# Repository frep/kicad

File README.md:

kicad
=====
workspace for [kicad](http://www.kicad-pcb.org/) projects

Links
-----
* A starting point to work with kicad could be the the linked [tutorial](http://store.curiousinventor.com/guides/kicad).
* To convert pictures to silkscreen graphics (in kicad_mod format), I used the following [tool](http://img2mod.wayneandlayne.com/)
* To prepare the generated kicad files for the [Seeedstudio Fusion Service](http://www.seeedstudio.com/service/index.php?r=pcb), follow these [instructions](http://koblents.com/Ches/Original-Work/46-KiCAD---Seeedstudio-Fusion--Getting-Started/).  

Generation of gerber files
--------------------------
*Hi,*
*I had some trouble making a correct submission to the Seeedstudio Fusion service. Just for the sake of documentation* *in case somebody looks for information regarding this topic:*
*From my experience here are the parameters that work well with seeedstudio fusion service:*
*When exporting your PCB layout, select both coper layers, both solder mask layers, both silkscreen layers, and the* *edge cut layer.*
*Select "exclude edges from other layers" (sorry my version of kicad is in french and right now I can't make it work* *in english so the option's name is not necessarily exact).*
*In format, select "4.6"*
*In the Gerber options select the Protel extensions. It will generate the files with the correct extensions* *".GTL",".GTS", ...*

*To create the drill file I used "Units : inches", "Suppress leading* 
*zeros", postscript format (I don't know if that's useful), minimal*
*header", absolute coordinates.*

*Put all the generated files in a Zip archive, it should work. In case*
*it doesn't seeedstudio sends a mail indicating the error and you can *
*re-submit your files.*

**There is no need to rename the files.**

*I worked for me using 2 sided PCBs.*
*Hope it helps*

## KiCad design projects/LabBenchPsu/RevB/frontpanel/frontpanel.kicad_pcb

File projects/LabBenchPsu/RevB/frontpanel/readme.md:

Frontpanel
==========

Working:
--------
 * reading buttons and encoders over gpio-expander
 * TPS2513: Loading iPhone (1A), iPad (1.5A)

Not working:
------------
 * LiPo charging indicators (2 leds) worked first, but not anymore. Maybe too low current resistor used?
 * Load on  indicator on the gpio-expander not working. Probably signal too low since it's taken after loadOn-diode.

More or less working:
---------------------
 * LiPo charger with different load currents works up to about 500mA. Imo it should work up to 1000mA. 

Not yet tested:
---------------
 * TPS2513: Loading android devices

Improvements for a next revision:
---------------------------------
 * Placement of the gpio-expander: out of the way from the display
 * LoadOn - signal should be read out correct.
 * Maybe adding an ina219 for measuring the load current of the LiPo charger. With this feedback, loadcurrent could be controlled.
 * Screw terminal have quite small diameters. Maybe use bigger ones or more of them (at least for 5V)

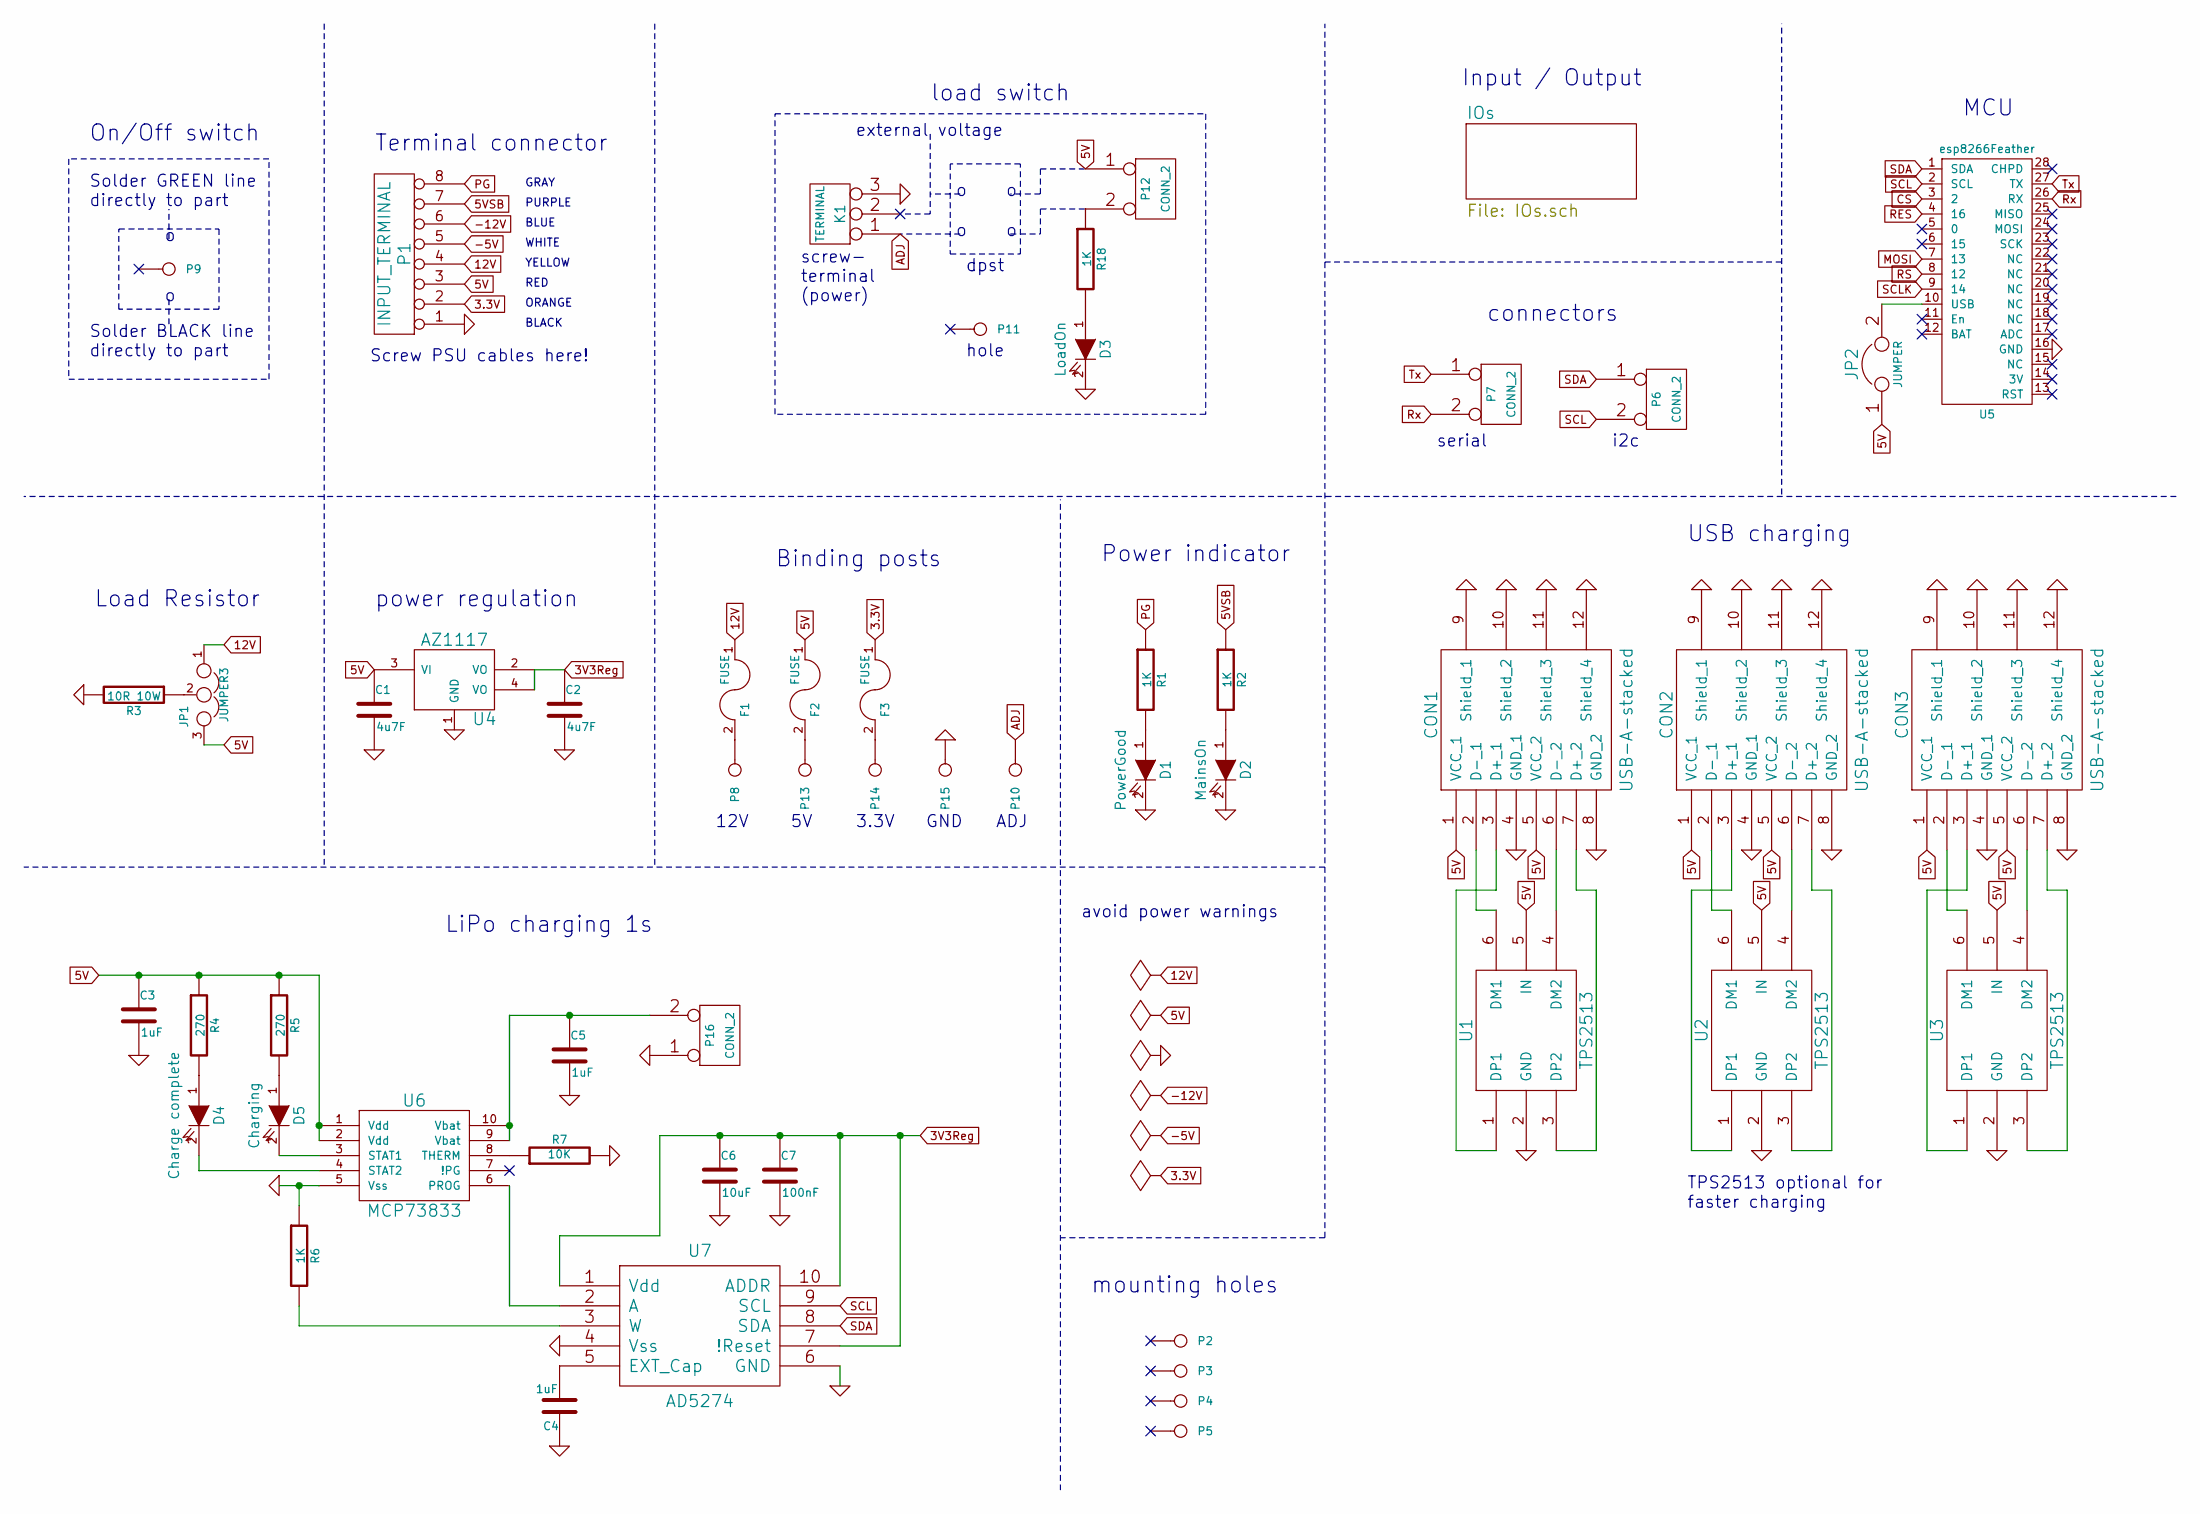
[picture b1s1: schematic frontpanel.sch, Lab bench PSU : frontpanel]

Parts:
C1, C2: 4u7F; C0805
C3, C4, C5: 1uF; C0805
C6: 10uF; C0805
C7: 100nF; C0805
CON1, CON2, CON3: USB-A-stacked; USB-A-Stacked
D1: PowerGood; LED-0805
D2: MainsOn; LED-0805
D3: LoadOn; LED-0805
D4: Charge complete; LED-0805
D5: Charging; LED-0805
F1, F2, F3: FUSE; C1812
JP1: JUMPER3; Pin_Proto_Straight_1x03
JP2: JUMPER; Pin_Proto_Straight_1x02
K1: TERMINAL; terminal_3p5mm_3pin
P1: INPUT_TERMINAL; terminal_3p5mm_8pin
P2, P3, P4, P5: MH; MountingHole_3mm
P6, P7, P12: CONN_2; Pin_Proto_Straight_1x02
P8, P10, P13, P14, P15: BindingPost
P9: OnOffSwitch; RockerSwitch
P11: LoadSwitch
P16: CONN_2; JST-PH-2-THM
R1, R2, R6, R18: 1K; R0805
R3: 10R 10W; R_ceramic_48x9p5x9mm
R4, R5: 270; R0805
R7: 10K; R0805
U1, U2, U3: TPS2513; SOT23-6
U4: AZ1117; SOT223
U5: esp8266Feather; featherEsp
U6: MCP73833; MSOP10
U7: AD5274; MSOP10

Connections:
3.3V: F3.1, P1.2
3V3Reg: C2.1, C6.1, C7.1, U4.2 (VO), U4.4 (VO), U7.1 (Vdd), U7.7 (!Reset), U7.10 (ADDR); also elsewhere on the board
5V: C1.1, C3.1, CON1.1 (VCC_1), CON1.5 (VCC_2), CON2.1 (VCC_1), CON2.5 (VCC_2), CON3.1 (VCC_1), CON3.5 (VCC_2), F2.1, JP1.3, JP2.1, P1.3, P12.1, R4.1, R5.1, U1.5 (IN), U2.5 (IN), U3.5 (IN), U4.3 (VI), U6.1 (Vdd), U6.2 (Vdd)
5VSB: P1.7, R2.1
12V: F1.1, JP1.1, P1.4
-5V: P1.5
-12V: P1.6
ADJ: K1.1, P10.1
CS: U5.3 (2); also elsewhere on the board
GND: C1.2, C2.2, C3.2, C4.1, C5.2, C6.2, C7.2, CON1.4 (GND_1), CON1.8 (GND_2), CON1.9 (Shield_1), CON1.10 (Shield_2), CON1.11 (Shield_3), CON1.12 (Shield_4), CON2.4 (GND_1), CON2.8 (GND_2), CON2.9 (Shield_1), CON2.10 (Shield_2), CON2.11 (Shield_3), CON2.12 (Shield_4), CON3.4 (GND_1), CON3.8 (GND_2), CON3.9 (Shield_1), CON3.10 (Shield_2), CON3.11 (Shield_3), CON3.12 (Shield_4), D1.2 (K), D2.2 (K), D3.2 (K), K1.3, P1.1, P15.1, P16.1, R3.2, R6.1, R7.2, U1.2 (GND), U2.2 (GND), U3.2 (GND), U4.1 (GND), U5.16 (GND), U6.5 (Vss), U7.4 (Vss), U7.6 (GND); also elsewhere on the board
MOSI: U5.7 (13); also elsewhere on the board
unnamed: C4.2, U7.5 (EXT_Cap)
unnamed: C5.1, P16.2 (PM), U6.9 (Vbat), U6.10 (Vbat)
unnamed: CON1.2 (D-_1), U1.6 (DM1)
unnamed: CON1.3 (D+_1), U1.1 (DP1)
unnamed: CON1.6 (D-_2), U1.4 (DM2)
unnamed: CON1.7 (D+_2), U1.3 (DP2)
unnamed: CON2.2 (D-_1), U2.6 (DM1)
unnamed: CON2.3 (D+_1), U2.1 (DP1)
unnamed: CON2.6 (D-_2), U2.4 (DM2)
unnamed: CON2.7 (D+_2), U2.3 (DP2)
unnamed: CON3.2 (D-_1), U3.6 (DM1)
unnamed: CON3.3 (D+_1), U3.1 (DP1)
unnamed: CON3.6 (D-_2), U3.4 (DM2)
unnamed: CON3.7 (D+_2), U3.3 (DP2)
unnamed: D1.1 (A), R1.2
unnamed: D2.1 (A), R2.2
unnamed: D3.1 (A), R18.2
unnamed: D4.1 (A), R4.2
unnamed: D4.2 (K), U6.4 (STAT2)
unnamed: D5.1 (A), R5.2
unnamed: D5.2 (K), U6.3 (STAT1)
unnamed: F1.2, P8.1
unnamed: F2.2, P13.1
unnamed: F3.2, P14.1
unnamed: JP1.2, R3.1
unnamed: JP2.2, U5.10 (USB)
unnamed: P12.2 (PM), R18.1
unnamed: R6.2, U7.3 (W)
unnamed: R7.1, U6.8 (THERM)
unnamed: U6.6 (PROG), U7.2 (A)
PG: P1.8, R1.1
RES: U5.4 (16); also elsewhere on the board
RS: U5.8 (12); also elsewhere on the board
Rx: P7.2 (PM), U5.26 (RX)
SCL: P6.2 (PM), U5.2 (SCL), U7.9 (SCL); also elsewhere on the board
SCLK: U5.9 (14); also elsewhere on the board
SDA: P6.1, U5.1 (SDA), U7.8 (SDA); also elsewhere on the board
Tx: P7.1, U5.27 (TX)

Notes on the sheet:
Solder GREEN line directly to part
Solder BLACK line directly to part
Terminal connector
GRAY
PURPLE
BLUE
WHITE
YELLOW
RED
ORANGE
BLACK
Load Resistor
mounting holes
serial
i2c
avoid power warnings
Binding posts
load switch
screw- terminal (power)
hole
12V
3.3V
GND
ADJ
dpst
external voltage
MCU
TPS2513 optional for faster charging
On/Off switch
LiPo charging 1s
USB charging
power regulation
connectors
Screw PSU cables here!
Input / Output
Power indicator

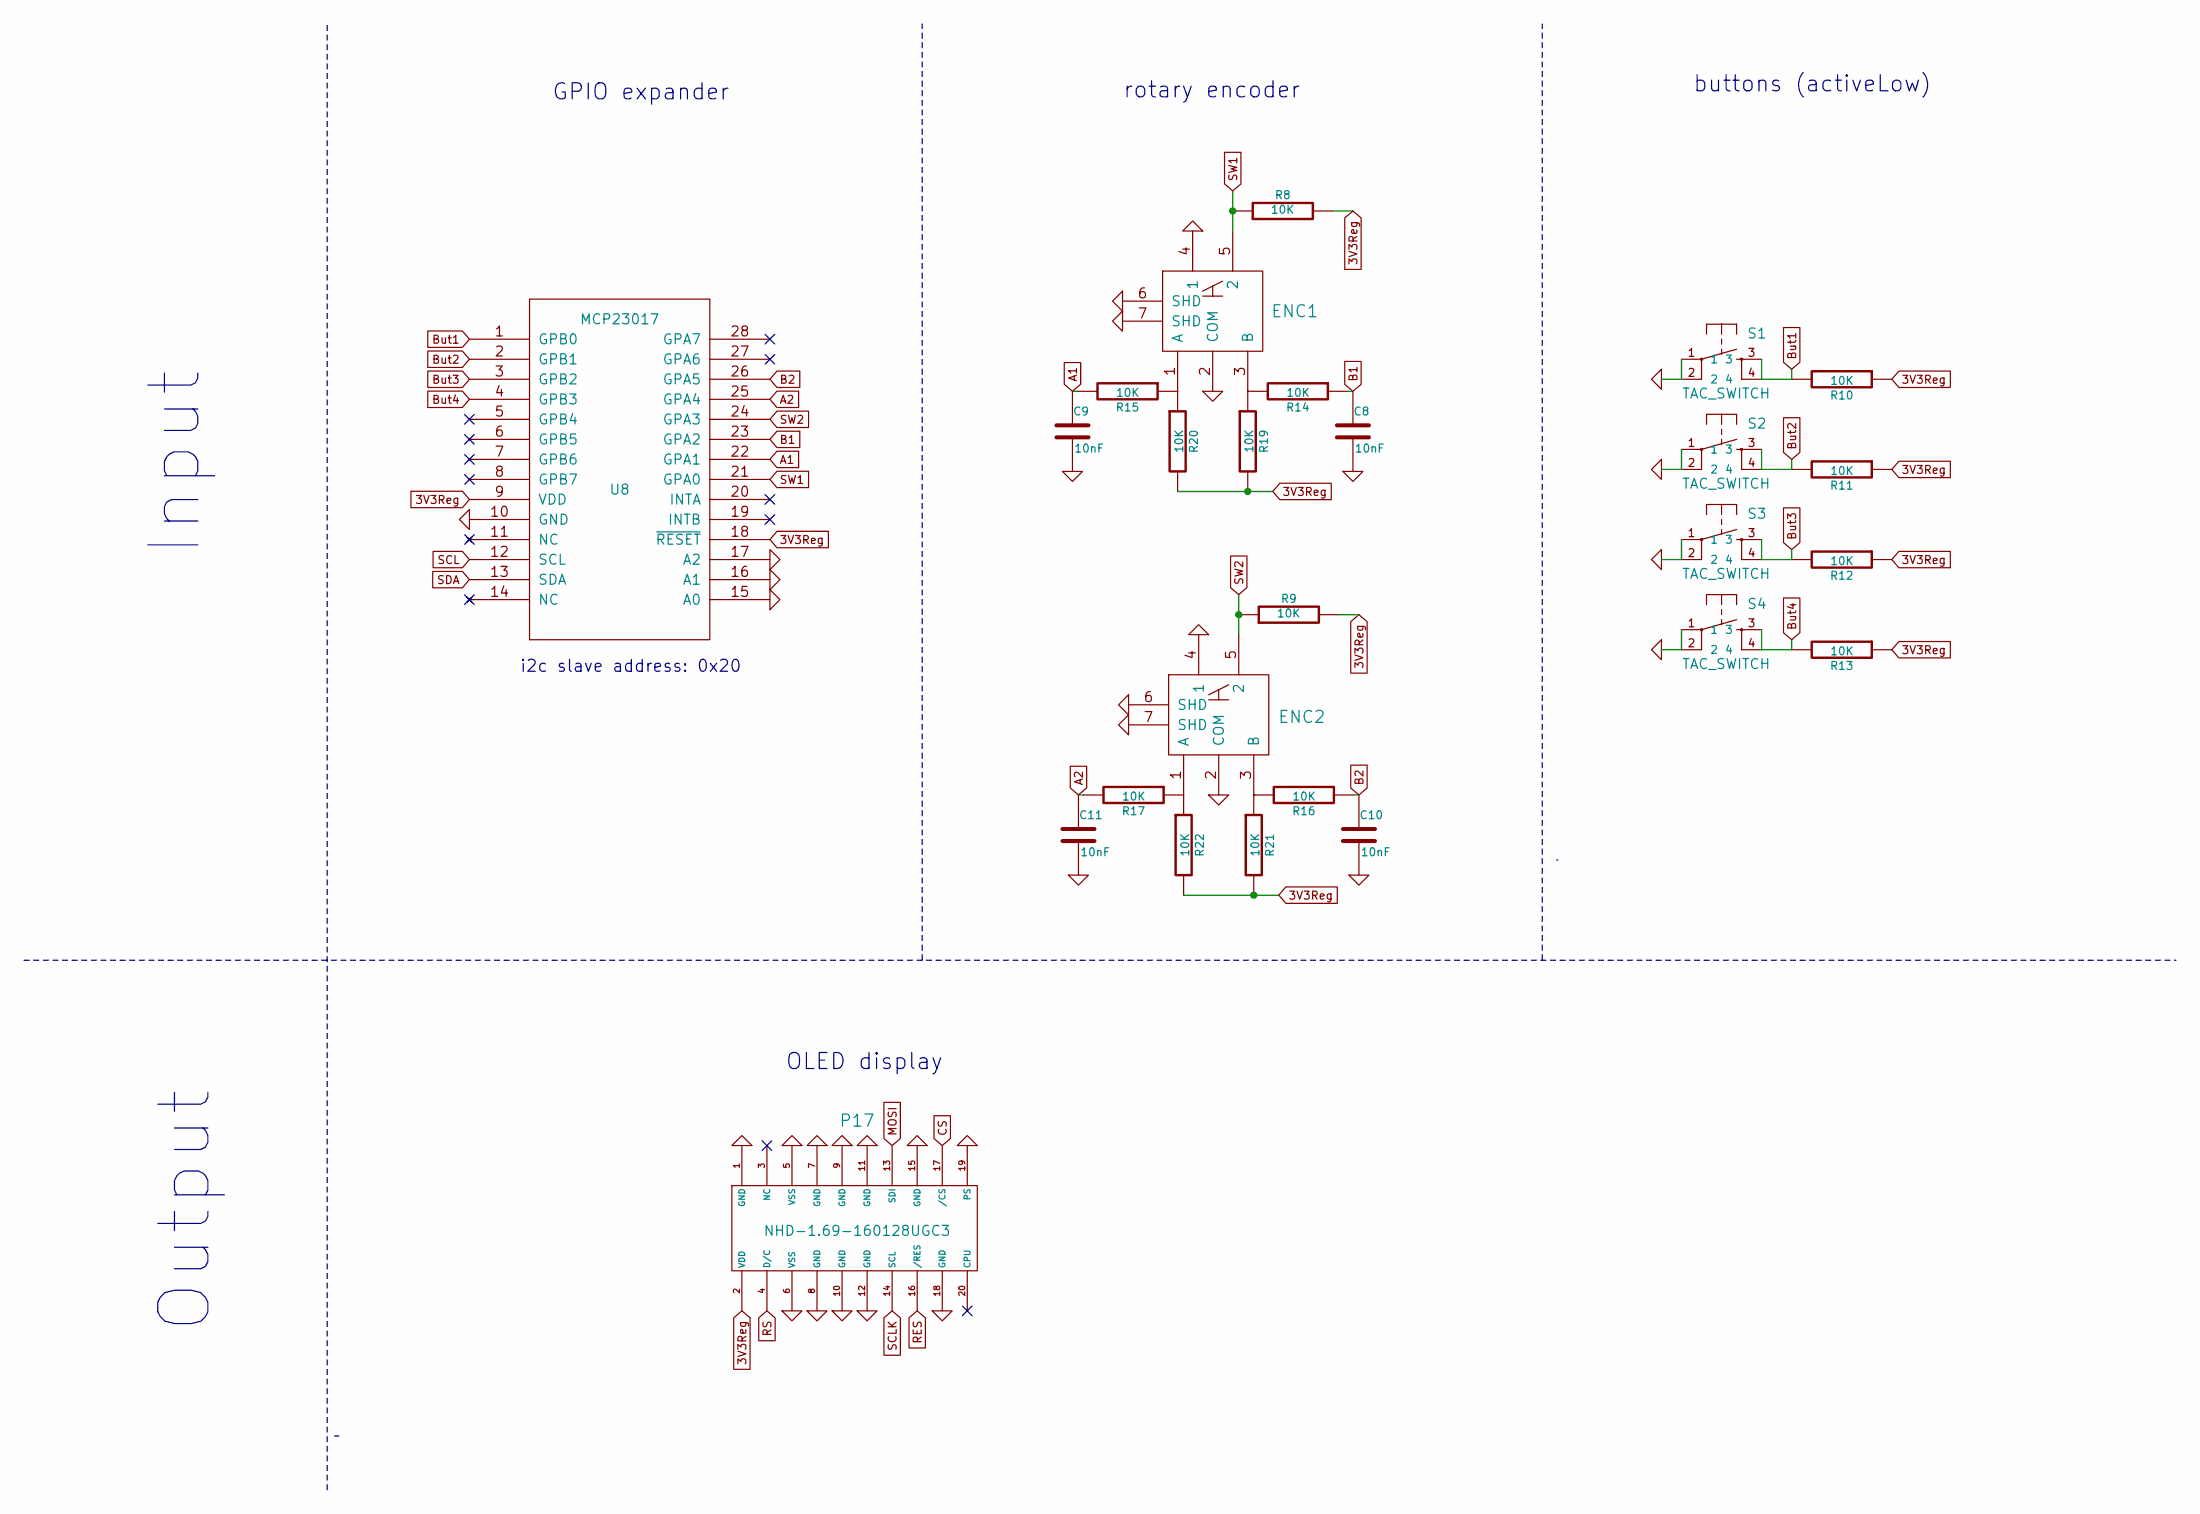
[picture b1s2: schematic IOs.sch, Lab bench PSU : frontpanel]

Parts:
C8, C9, C10, C11: 10nF; C0805
ENC1, ENC2: RotaryEncoder
P17: NHD-1.69-160128UGC3
R8, R9, R10, R11, R12, R13, R14, R15, R16, R17, R19, R20, R21, R22: 10K; R0805
S1, S2, S3, S4: TAC_SWITCH; TACTILE-PTH
U8: MCP23017; SOIC28W

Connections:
3V3Reg: P17.2 (VDD), R8.2, R9.2, R10.1, R11.1, R12.1, R13.1, R19.2, R20.2, R21.2, R22.2, U8.9 (VDD), U8.18 (~RESET); also elsewhere on the board
A1: C9.1, R15.2, U8.22 (GPA1)
A2: C11.1, R17.2, U8.25 (GPA4)
B1: C8.1, R14.1, U8.23 (GPA2)
B2: C10.1, R16.1, U8.26 (GPA5)
But1: R10.2, S1.3, S1.4, U8.1 (GPB0)
But2: R11.2, S2.3, S2.4, U8.2 (GPB1)
But3: R12.2, S3.3, S3.4, U8.3 (GPB2)
But4: R13.2, S4.3, S4.4, U8.4 (GPB3)
CS: P17.17 (/CS); also elsewhere on the board
GND: C8.2, C9.2, C10.2, C11.2, ENC1.2 (COM), ENC1.4 (1), ENC1.6 (SHD), ENC1.7 (SHD), ENC2.2 (COM), ENC2.4 (1), ENC2.6 (SHD), ENC2.7 (SHD), P17.1 (GND), P17.5 (VSS), P17.6 (VSS), P17.7 (GND), P17.8 (GND), P17.9 (GND), P17.10 (GND), P17.11 (GND), P17.12 (GND), P17.15 (GND), P17.18 (GND), P17.19 (PS), S1.1, S1.2, S2.1, S2.2, S3.1, S3.2, S4.1, S4.2, U8.10 (GND), U8.15 (A0), U8.16 (A1), U8.17 (A2); also elsewhere on the board
MOSI: P17.13 (SDI); also elsewhere on the board
unnamed: ENC1.1 (A), R15.1, R20.1
unnamed: ENC1.3 (B), R14.2, R19.1
unnamed: ENC2.1 (A), R17.1, R22.1
unnamed: ENC2.3 (B), R16.2, R21.1
RES: P17.16 (/RES); also elsewhere on the board
RS: P17.4 (D/C); also elsewhere on the board
SCL: U8.12 (SCL); also elsewhere on the board
SCLK: P17.14 (SCL); also elsewhere on the board
SDA: U8.13 (SDA); also elsewhere on the board
SW1: ENC1.5 (2), R8.1, U8.21 (GPA0)
SW2: ENC2.5 (2), R9.1, U8.24 (GPA3)

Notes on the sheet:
buttons (activeLow)
i2c slave address: 0x20
OLED display
Output
Input
GPIO expander
rotary encoder

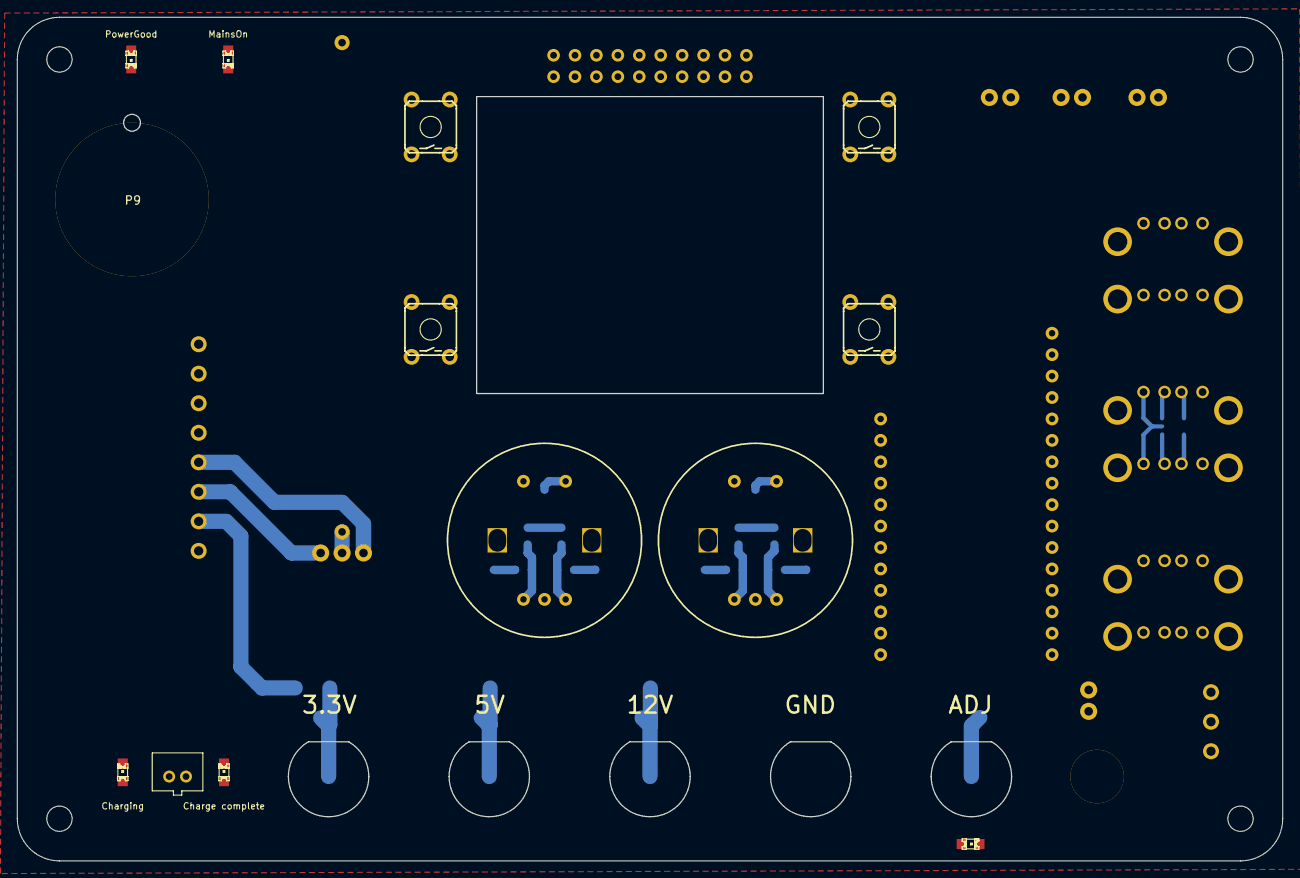
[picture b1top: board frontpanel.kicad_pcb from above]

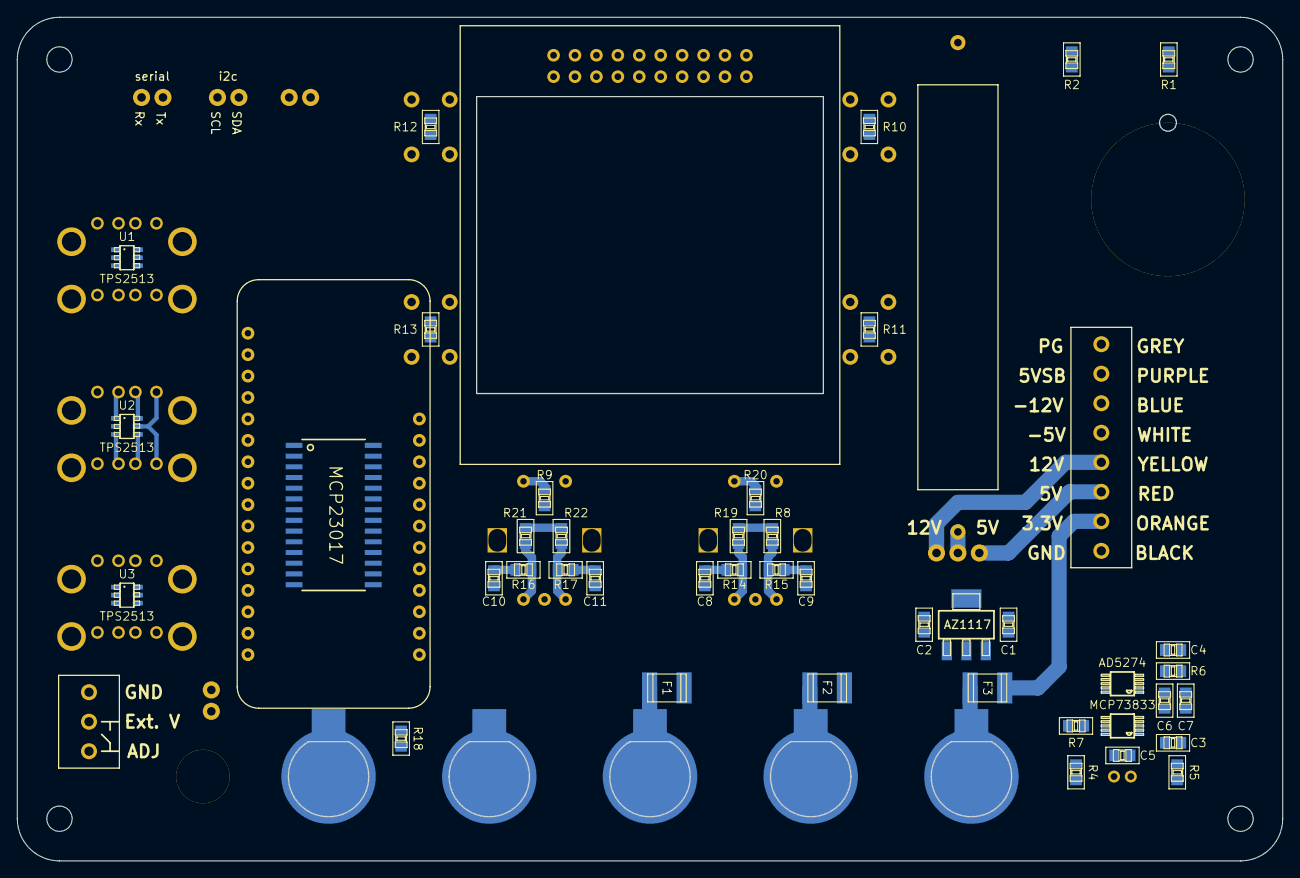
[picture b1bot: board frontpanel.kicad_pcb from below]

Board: 2 copper layers, 150.0 x 100.0 mm, 78 parts (54 on the bottom side), 61 nets.

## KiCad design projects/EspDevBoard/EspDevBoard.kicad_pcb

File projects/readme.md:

Projects
========
The following projects contains a pcb designed with kicad. All the needed schematics and footprints can be found in the library folder.   

Radxa Arduino Shield
--------------------
The RAS (Radxa Arduino Shield) is an addon-shield for the radxa rock (pro). It contains an arduino micro clone running at 3.3V connected over i2c with the radxa. The shield also includes an OLED 16x2 char display, also connected over i2c. It can be used by the radxa or the arduino.   

Lab bench PSU
-------------
A current-controlled, voltage-controlled lab bench psu based on the [usupply](http://www.eevblog.com/projects/usupply/) from David Jones. Instead of being portable, my focus is to transform an old pc-psu into an lab bench psu.

Arduino Controller
------------------
An Arduino-clone of the Arduino Esplora. I removed the things I didn't like and added some other features instead. 

PowerBox
--------
LiPo-cell in a box. Based on the Adafruit PowerBoost 1000 Charger. Charge Lipo-cell, power usb-devices from Lipo or use lipo as USP.
Measure Voltage and current drawn by the load. Autoshutdown, when critical lipo-voltage is reached.

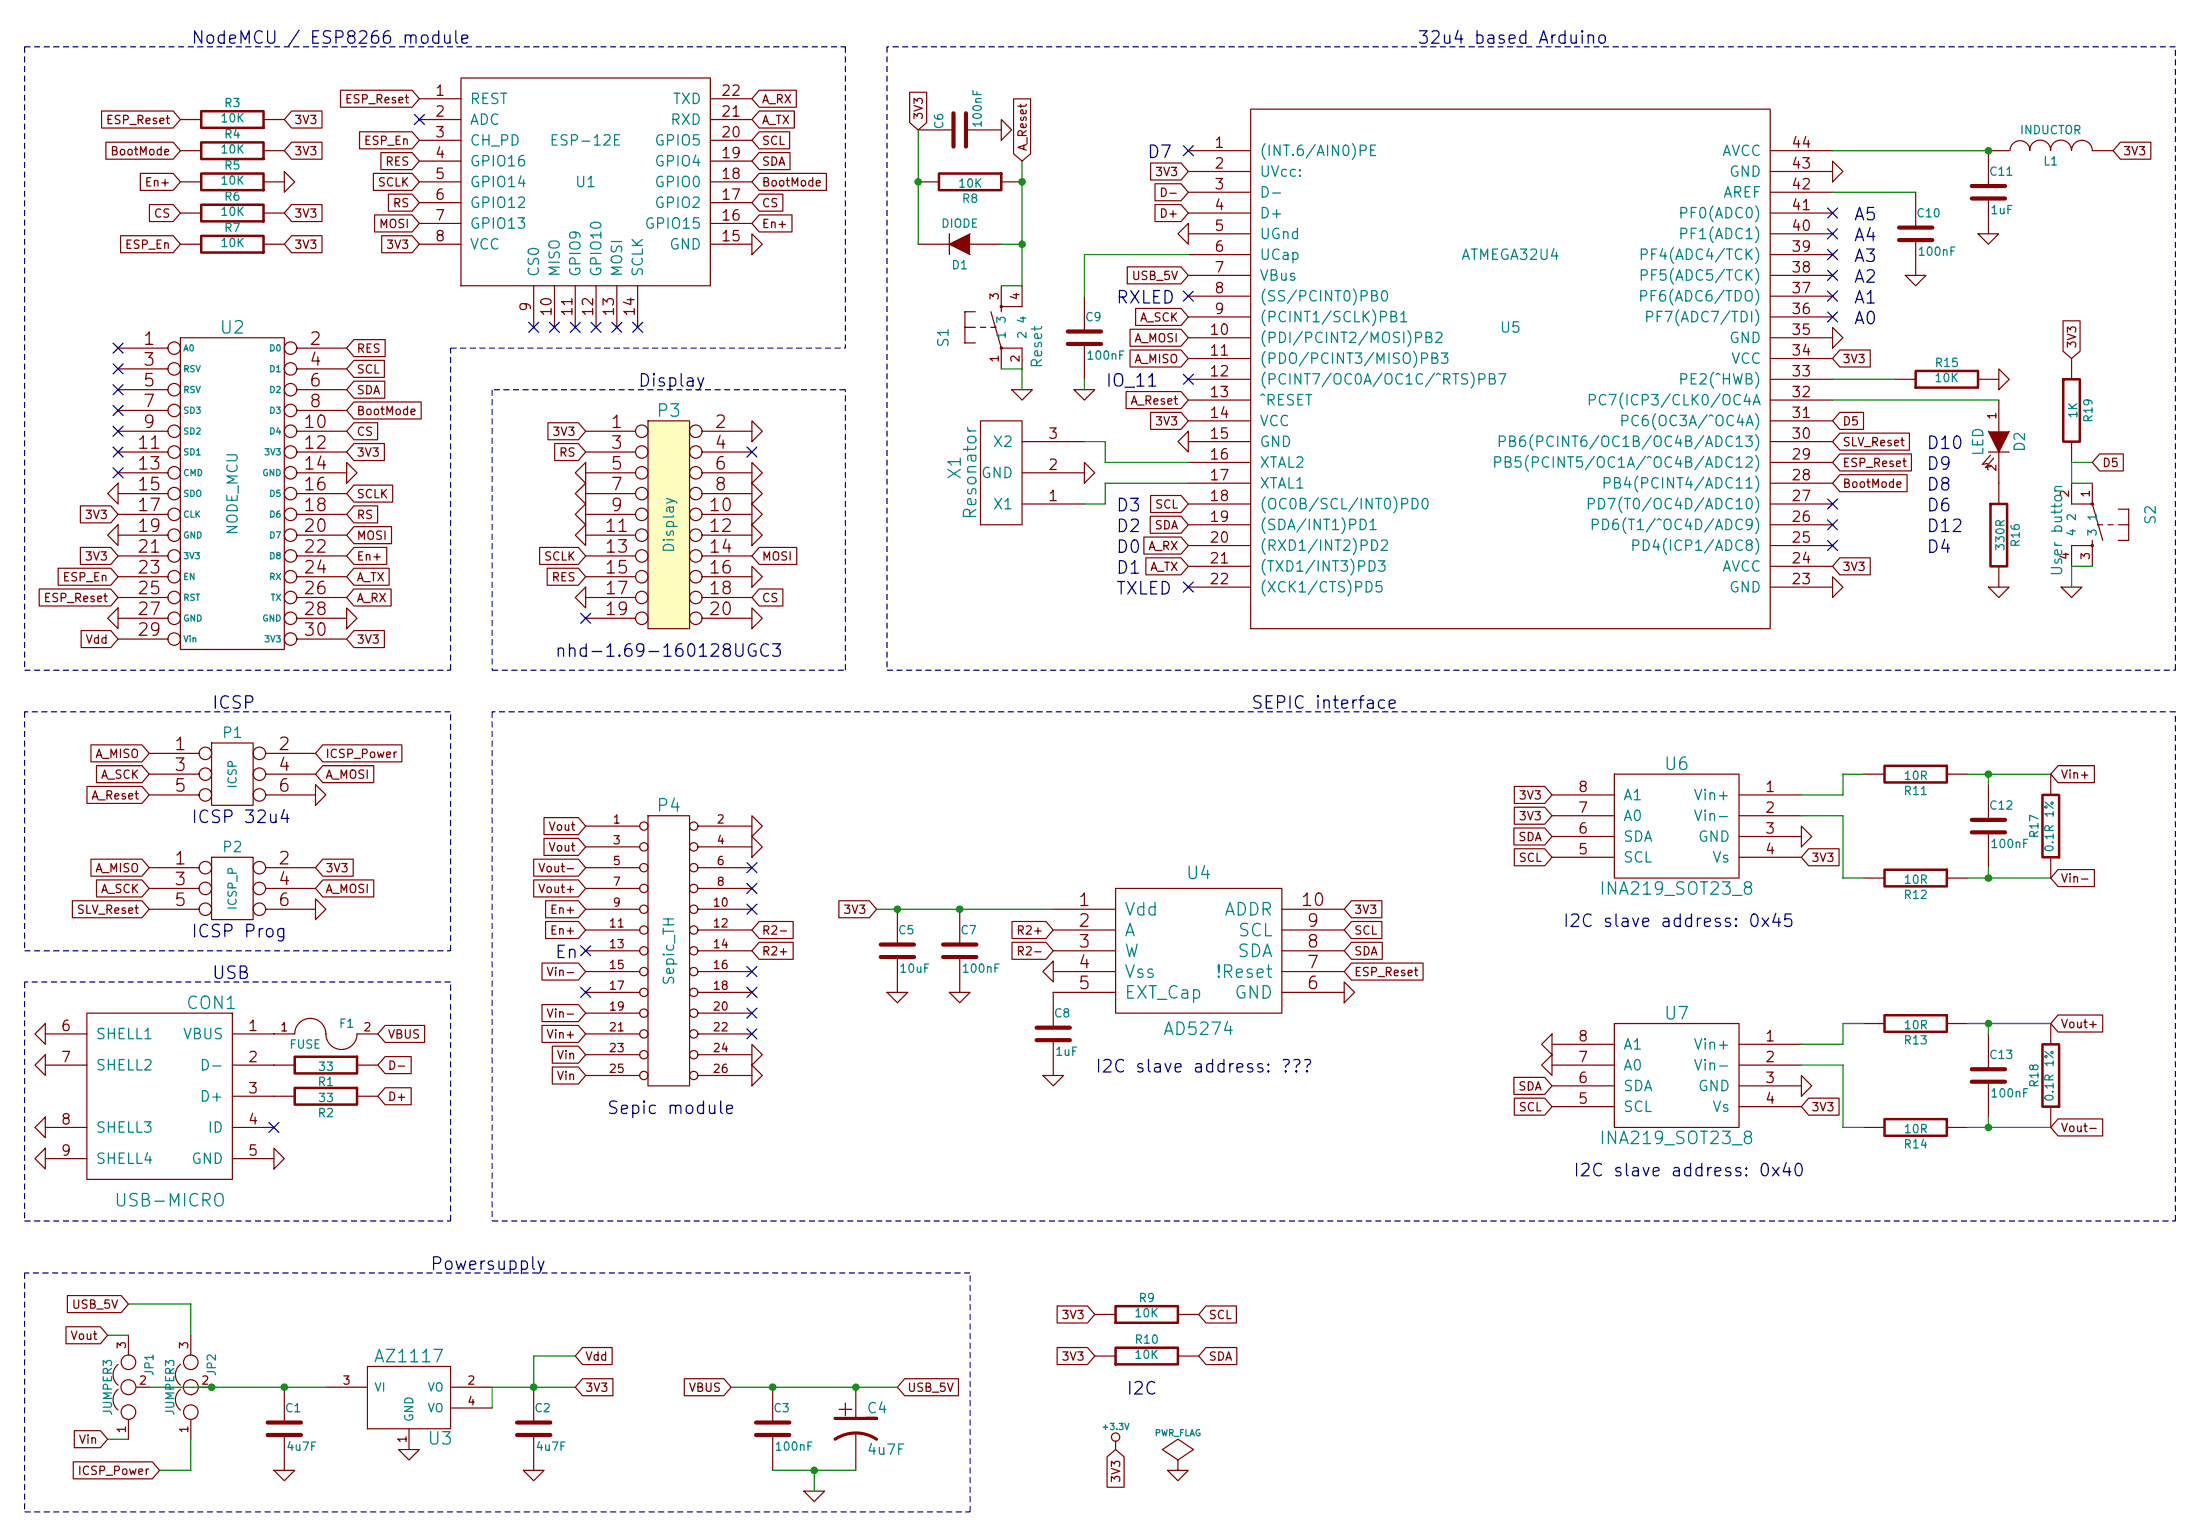
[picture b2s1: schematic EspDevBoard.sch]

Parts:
C1, C2, C4: 4u7F; C0805
C3, C6, C7, C9, C10, C12, C13: 100nF; C0805
C5: 10uF; C0805
C8, C11: 1uF; C0805
CON1: USB-MICRO; USB_Micro
D1: DIODE; Diode-MiniMELF_Handsoldering
D2: LED; LED-0805
F1: FUSE; C1812
JP1, JP2: JUMPER3; Pin_Proto_Straight_1x03
L1: INDUCTOR; C0805
P1: ICSP; Pin_Proto_Straight_2x03
P2: ICSP_P; Pin_Proto_Straight_2x03
P3: Display; Pin_Proto_Straight_2x10
P4: Sepic_TH
R1, R2: 33; R0805
R3, R4, R5, R6, R7, R8, R9, R10, R15: 10K; R0805
R11, R12, R13, R14: 10R; R0805
R16: 330R; R0805
R17, R18: 0.1R 1%; R1206
R19: 1K; R0805
S1: Reset; TACTILE-PTH
S2: User button; TACTILE-PTH
U1: ESP-12E
U2: NODE_MCU; NodeMcu
U3: AZ1117; SOT223
U4: AD5274; MSOP10
U5: ATMEGA32U4; TQFP44
U6, U7: INA219_SOT23_8; SOT-23-8
X1: Resonator

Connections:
3V3: C2.1, C5.1, C6.1, C7.1, D1.2 (K), L1.2, P2.2, P3.1, R3.1, R4.1, R6.1, R7.1, R8.2, R9.1, R10.1, R19.1, U1.8 (VCC), U2.12 (3V3), U2.17 (CLK), U2.21 (3V3), U2.29 (Vin), U2.30 (3V3), U3.2 (VO), U3.4 (VO), U4.1 (Vdd), U4.10 (ADDR), U5.2 (UVcc:), U5.14 (VCC), U5.24 (AVCC), U5.34 (VCC), U6.4 (Vs), U6.7 (A0), U6.8 (A1), U7.4 (Vs)
A_MISO: P1.1, P2.1, U5.11 ((PDO/PCINT3/MISO)PB3)
A_MOSI: P1.4, P2.4, U5.10 ((PDI/PCINT2/MOSI)PB2)
A_RX: U1.22 (TXD), U2.26 (TX), U5.20 ((RXD1/INT2)PD2)
A_Reset: D1.1 (A), P1.5, R8.1, S1.3, S1.4, U5.13 (^RESET)
A_SCK: P1.3, P2.3, U5.9 ((PCINT1/SCLK)PB1)
A_TX: U1.21 (RXD), U2.24 (RX), U5.21 ((TXD1/INT3)PD3)
BootMode: R4.2, U1.18 (GPIO0), U2.8 (D3), U5.28 (PB4(PCINT4/ADC11))
CS: P3.18, R6.2, U1.17 (GPIO2), U2.10 (D4)
D5: R19.2, S2.1, S2.2, U5.31 (PC6(OC3A/^OC4A))
D+: R2.1, U5.4 (D+)
D-: R1.1, U5.3 (D-)
ESP_En: R7.2, U1.3 (CH_PD), U2.23 (EN)
ESP_Reset: R3.2, U1.1 (REST), U2.25 (RST), U4.7 (!Reset), U5.29 (PB5(PCINT5/OC1A/^OC4B/ADC12))
En+: P4.9, P4.11, R5.2, U1.16 (GPIO15), U2.22 (D8)
GND: C1.2, C2.2, C3.2, C4.2, C5.2, C6.2, C7.2, C8.2, C9.2, C10.2, C11.2, CON1.5 (GND), CON1.6 (SHELL1), CON1.7 (SHELL2), CON1.8 (SHELL3), CON1.9 (SHELL4), P1.6, P2.6, P3.2, P3.5, P3.6, P3.7, P3.8, P3.9, P3.10, P3.11, P3.12, P3.16, P3.17, P3.20, P4.2, P4.4, P4.24 (P20), P4.26 (P22), R5.1, R15.2, R16.2, S1.1, S1.2, S2.3, S2.4, U1.15 (GND), U2.14 (GND), U2.15 (SDO), U2.19 (GND), U2.27 (GND), U2.28 (GND), U3.1 (GND), U4.4 (Vss), U4.6 (GND), U5.5 (UGnd), U5.15 (GND), U5.23 (GND), U5.35 (GND), U5.43 (GND), U6.3 (GND), U7.3 (GND), U7.7 (A0), U7.8 (A1), X1.2 (GND)
ICSP_Power: JP2.1, P1.2
MOSI: P3.14, U1.7 (GPIO13), U2.20 (D7)
unnamed: C1.1, JP1.2, JP2.2, U3.3 (VI)
unnamed: C8.1, U4.5 (EXT_Cap)
unnamed: C9.1, U5.6 (UCap)
unnamed: C10.1, U5.42 (AREF)
unnamed: C11.1, L1.1, U5.44 (AVCC)
unnamed: CON1.1 (VBUS), F1.1
unnamed: CON1.2 (D-), R1.2
unnamed: CON1.3 (D+), R2.2
unnamed: D2.1 (A), U5.32 (PC7(ICP3/CLK0/OC4A)
unnamed: D2.2 (K), R16.1
unnamed: R11.2, U6.1 (Vin+)
unnamed: R12.2, U6.2 (Vin-)
unnamed: R13.2, U7.1 (Vin+)
unnamed: R14.2, U7.2 (Vin-)
unnamed: R15.1, U5.33 (PE2(^HWB))
unnamed: U5.16 (XTAL2), X1.3 (X2)
unnamed: U5.17 (XTAL1), X1.1 (X1)
R2+: P4.14, U4.2 (A)
R2-: P4.12, U4.3 (W)
RES: P3.15, U1.4 (GPIO16), U2.2 (D0)
RS: P3.3, U1.6 (GPIO12), U2.18 (D6)
SCL: R9.2, U1.20 (GPIO5), U2.4 (D1), U4.9 (SCL), U5.18 ((OC0B/SCL/INT0)PD0), U6.5 (SCL), U7.5 (SCL)
SCLK: P3.13, U1.5 (GPIO14), U2.16 (D5)
SDA: R10.2, U1.19 (GPIO4), U2.6 (D2), U4.8 (SDA), U5.19 ((SDA/INT1)PD1), U6.6 (SDA), U7.6 (SDA)
SLV_Reset: P2.5, U5.30 (PB6(PCINT6/OC1B/OC4B/ADC13))
VBUS: C3.1, C4.1, F1.2, JP2.3, U5.7 (VBus)
Vin: JP1.1, P4.23, P4.25 (P24)
Vin+: C12.1, P4.21, R11.1, R17.2
Vin-: C12.2, P4.15, P4.19, R12.1, R17.1
Vout: JP1.3, P4.1, P4.3
Vout+: C13.1, P4.7, R13.1, R18.2
Vout-: C13.2, P4.5, R14.1, R18.1

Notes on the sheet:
Display
Sepic module
ICSP 32u4
I2C
I2C slave address: 0x40
I2C slave address: 0x45
ICSP Prog
I2C slave address: ???
RXLED
TXLED
D10
D12
ICSP
NodeMCU / ESP8266 module
USB
32u4 based Arduino
SEPIC interface
Powersupply
nhd-1.69-160128UGC3
IO_11

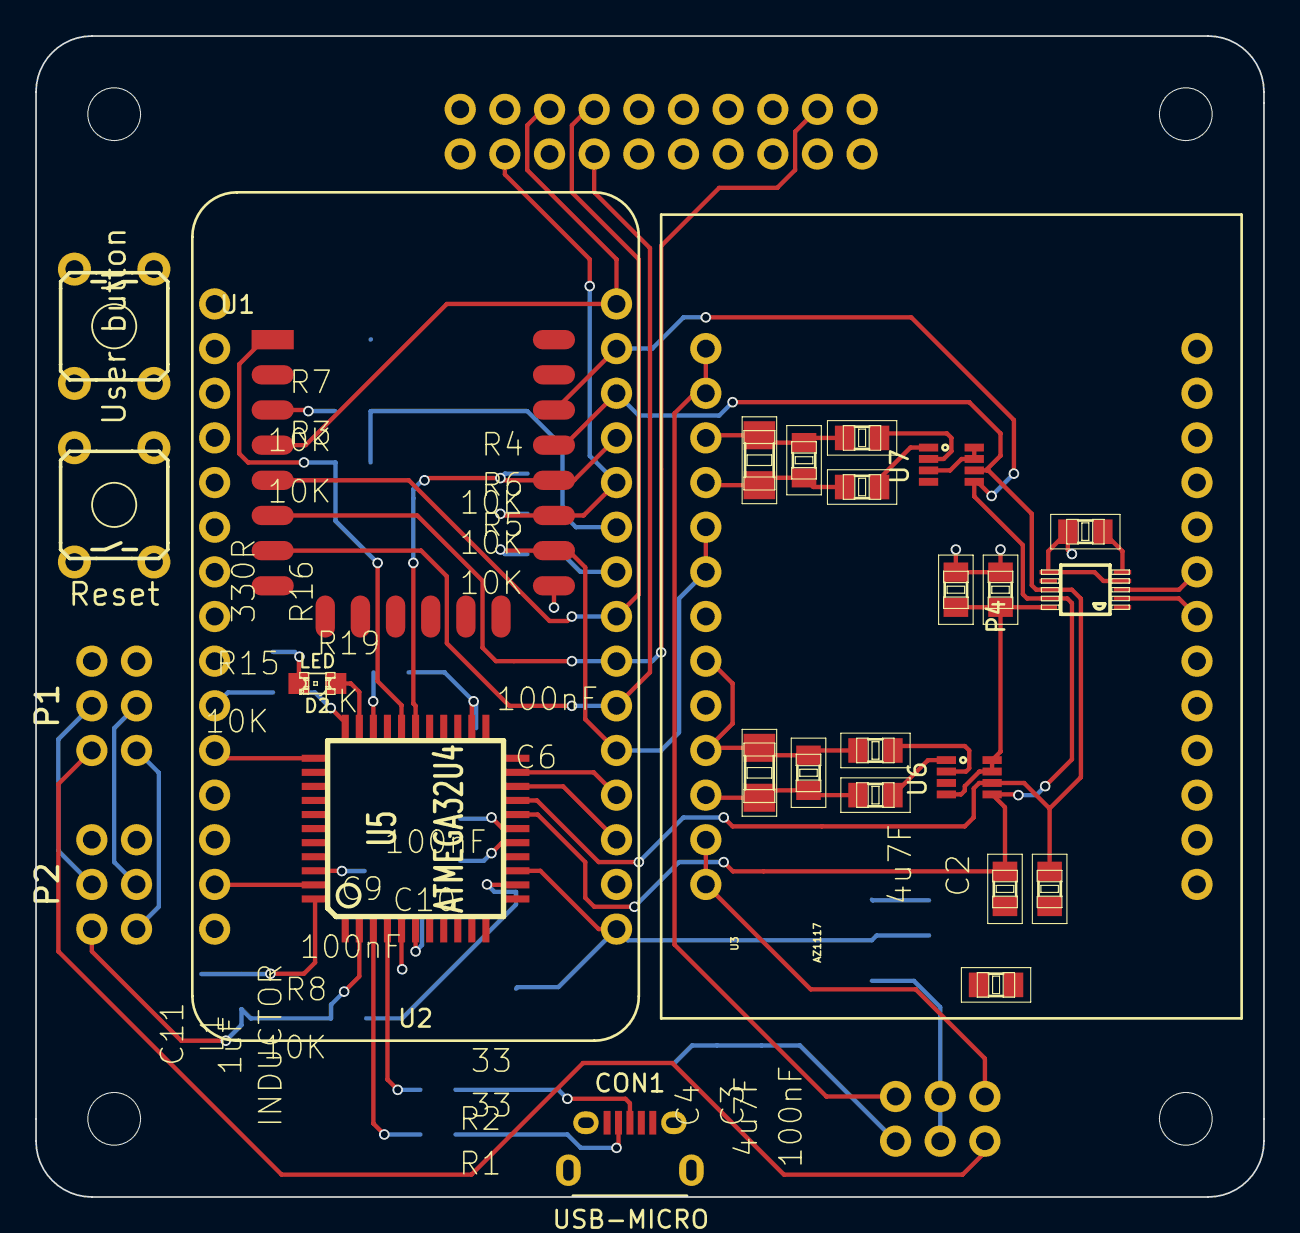
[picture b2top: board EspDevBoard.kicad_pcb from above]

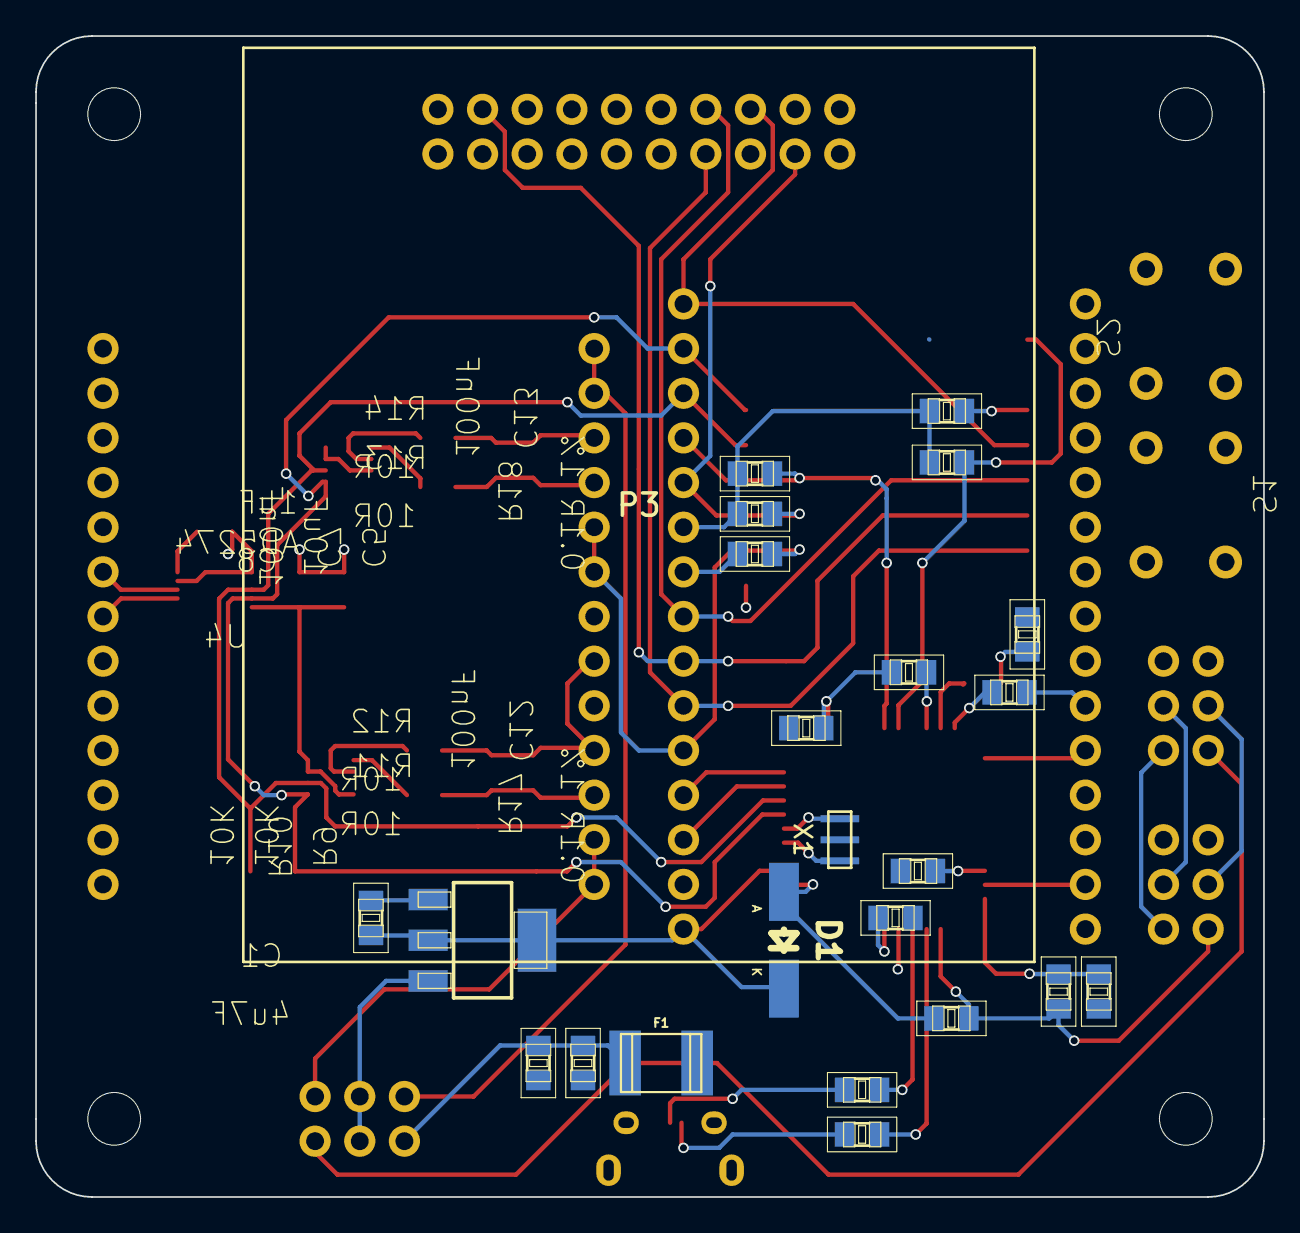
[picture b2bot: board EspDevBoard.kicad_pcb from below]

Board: 2 copper layers, 69.9 x 66.0 mm, 57 parts (24 on the bottom side), 50 nets.

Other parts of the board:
P5, P6, P7, P8: CONN_1; MountingHole_3mm
